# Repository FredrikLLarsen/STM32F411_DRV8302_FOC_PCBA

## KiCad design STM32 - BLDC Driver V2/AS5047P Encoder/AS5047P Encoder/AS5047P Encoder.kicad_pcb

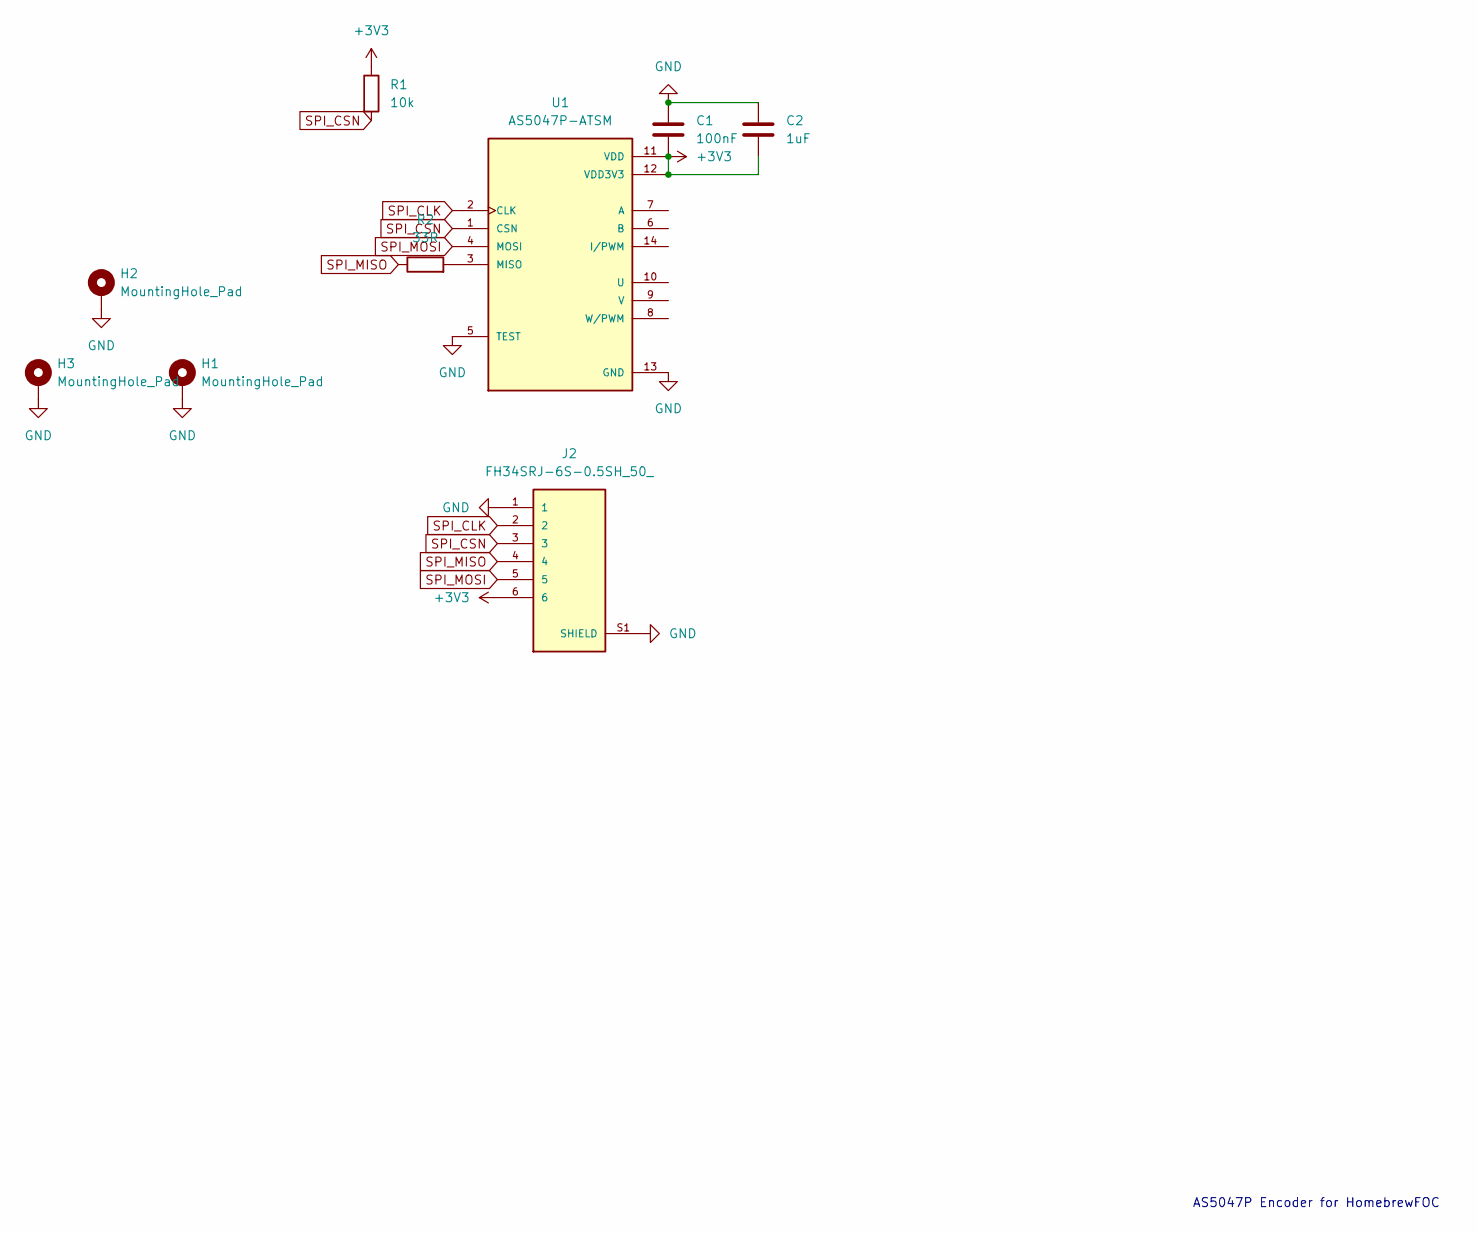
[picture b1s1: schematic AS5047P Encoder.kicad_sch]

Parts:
C1: 100nF; C_0603_1608Metric_Pad1.08x0.95mm_HandSolder
C2: 1uF; C_0603_1608Metric_Pad1.08x0.95mm_HandSolder
H1, H2, H3: MountingHole_Pad; MountingHole_3.2mm_M3_ISO7380_Pad
J2: FH34SRJ-6S-0.5SH_50_; HRS_FH34SRJ-6S-0.5SH_50_
R1: 10k; R_0603_1608Metric_Pad0.98x0.95mm_HandSolder
R2: 33R; R_0603_1608Metric_Pad0.98x0.95mm_HandSolder
U1: AS5047P-ATSM; SOP65P640X120-14N; PARTREV 1-01

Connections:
+3V3: C1.2, C2.2, J2.6, R1.1, U1.11 (VDD), U1.12 (VDD3V3)
GND: C1.1, C2.1, H1.1, H2.1, H3.1, J2.1, J2.S1 (SHIELD), J2.S2 (SHIELD), U1.5 (TEST), U1.13 (GND)
unnamed: R2.2, U1.3 (MISO)
SPI_CLK: J2.2, U1.2 (CLK)
SPI_CSN: J2.3, R1.2, U1.1 (CSN)
SPI_MISO: J2.4, R2.1
SPI_MOSI: J2.5, U1.4 (MOSI)

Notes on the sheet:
AS5047P Encoder for HomebrewFOC

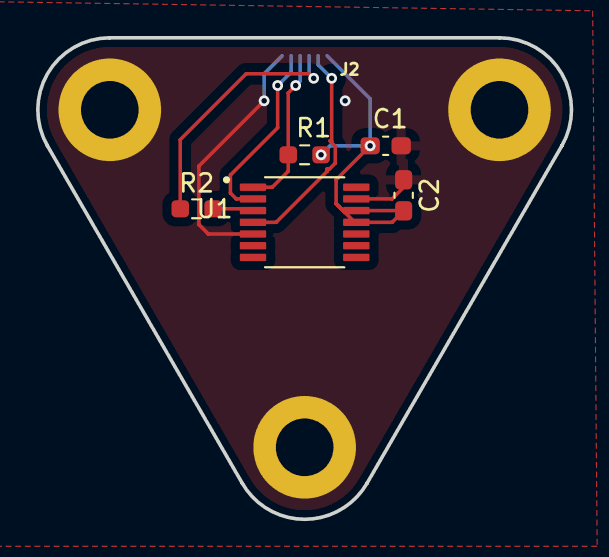
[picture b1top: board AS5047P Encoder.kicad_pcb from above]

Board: 2 copper layers, 29.7 x 26.8 mm, 9 parts (1 on the bottom side), 7 nets.

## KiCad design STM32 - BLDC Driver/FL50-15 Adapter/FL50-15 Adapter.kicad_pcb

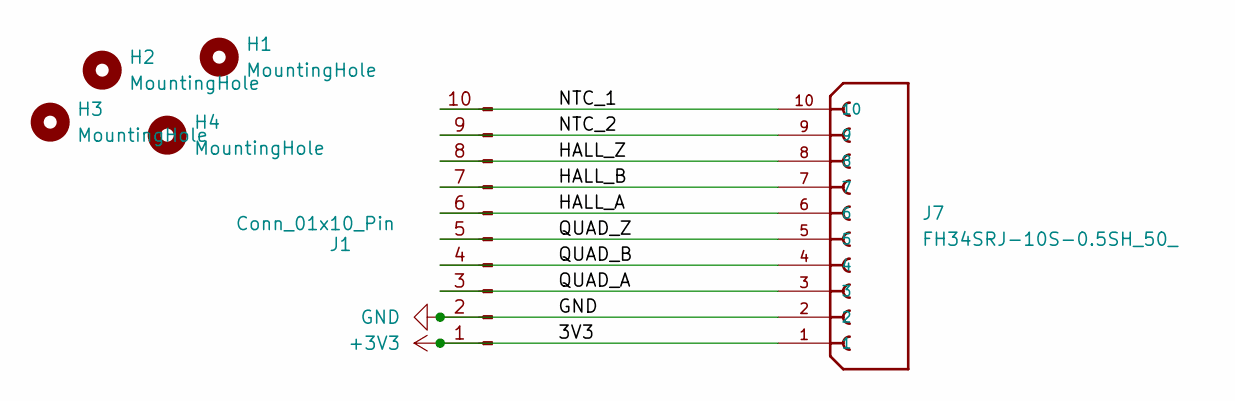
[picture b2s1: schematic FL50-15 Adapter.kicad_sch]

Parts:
H1, H2, H3, H4: MountingHole; MountingHole_3.2mm_M3
J1: Conn_01x10_Pin; PinHeader_1x10_P2.54mm_Vertical
J7: FH34SRJ-10S-0.5SH_50_; HRS_FH34SRJ-10S-0.5SH_50_; PARTREV Apr.1.2022

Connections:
+3V3: J1.1, J7.1
/HALL_A: J1.6, J7.6
/HALL_B: J1.7, J7.7
/HALL_Z: J1.8, J7.8
/NTC_1: J1.10, J7.10
/NTC_2: J1.9, J7.9
/QUAD_A: J1.3, J7.3
/QUAD_B: J1.4, J7.4
/QUAD_Z: J1.5, J7.5
GND: J1.2, J7.2

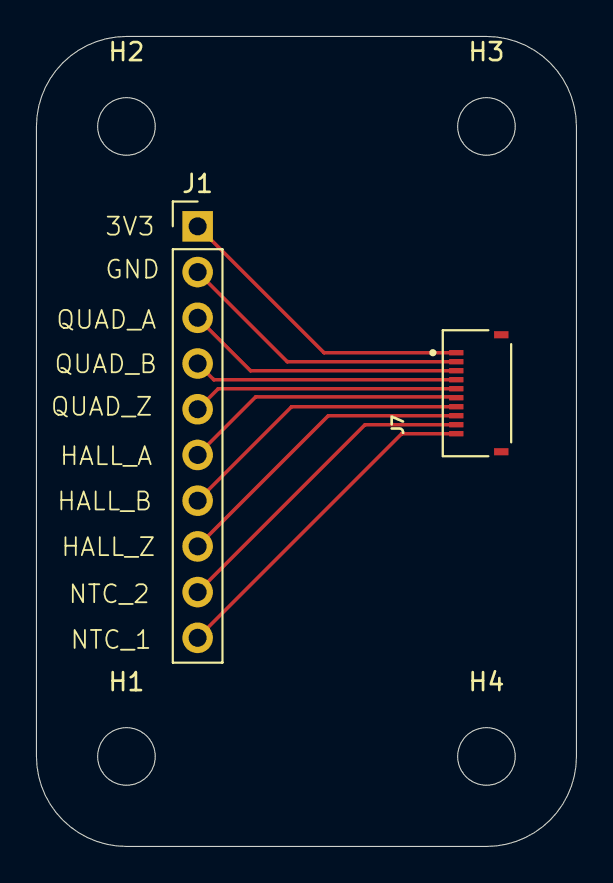
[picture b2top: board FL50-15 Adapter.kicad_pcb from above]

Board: 2 copper layers, 30.0 x 45.0 mm, 6 parts (0 on the bottom side), 10 nets.

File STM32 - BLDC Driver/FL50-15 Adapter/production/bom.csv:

Designator,Footprint,Quantity,Value,LCSC Part #
J1,PinHeader_1x10_P2.54mm_Vertical,1,Conn_01x10_Pin,
J7,HRS_FH34SRJ-10S-0.5SH_50_,1,FH34SRJ-10S-0.5SH_50_,

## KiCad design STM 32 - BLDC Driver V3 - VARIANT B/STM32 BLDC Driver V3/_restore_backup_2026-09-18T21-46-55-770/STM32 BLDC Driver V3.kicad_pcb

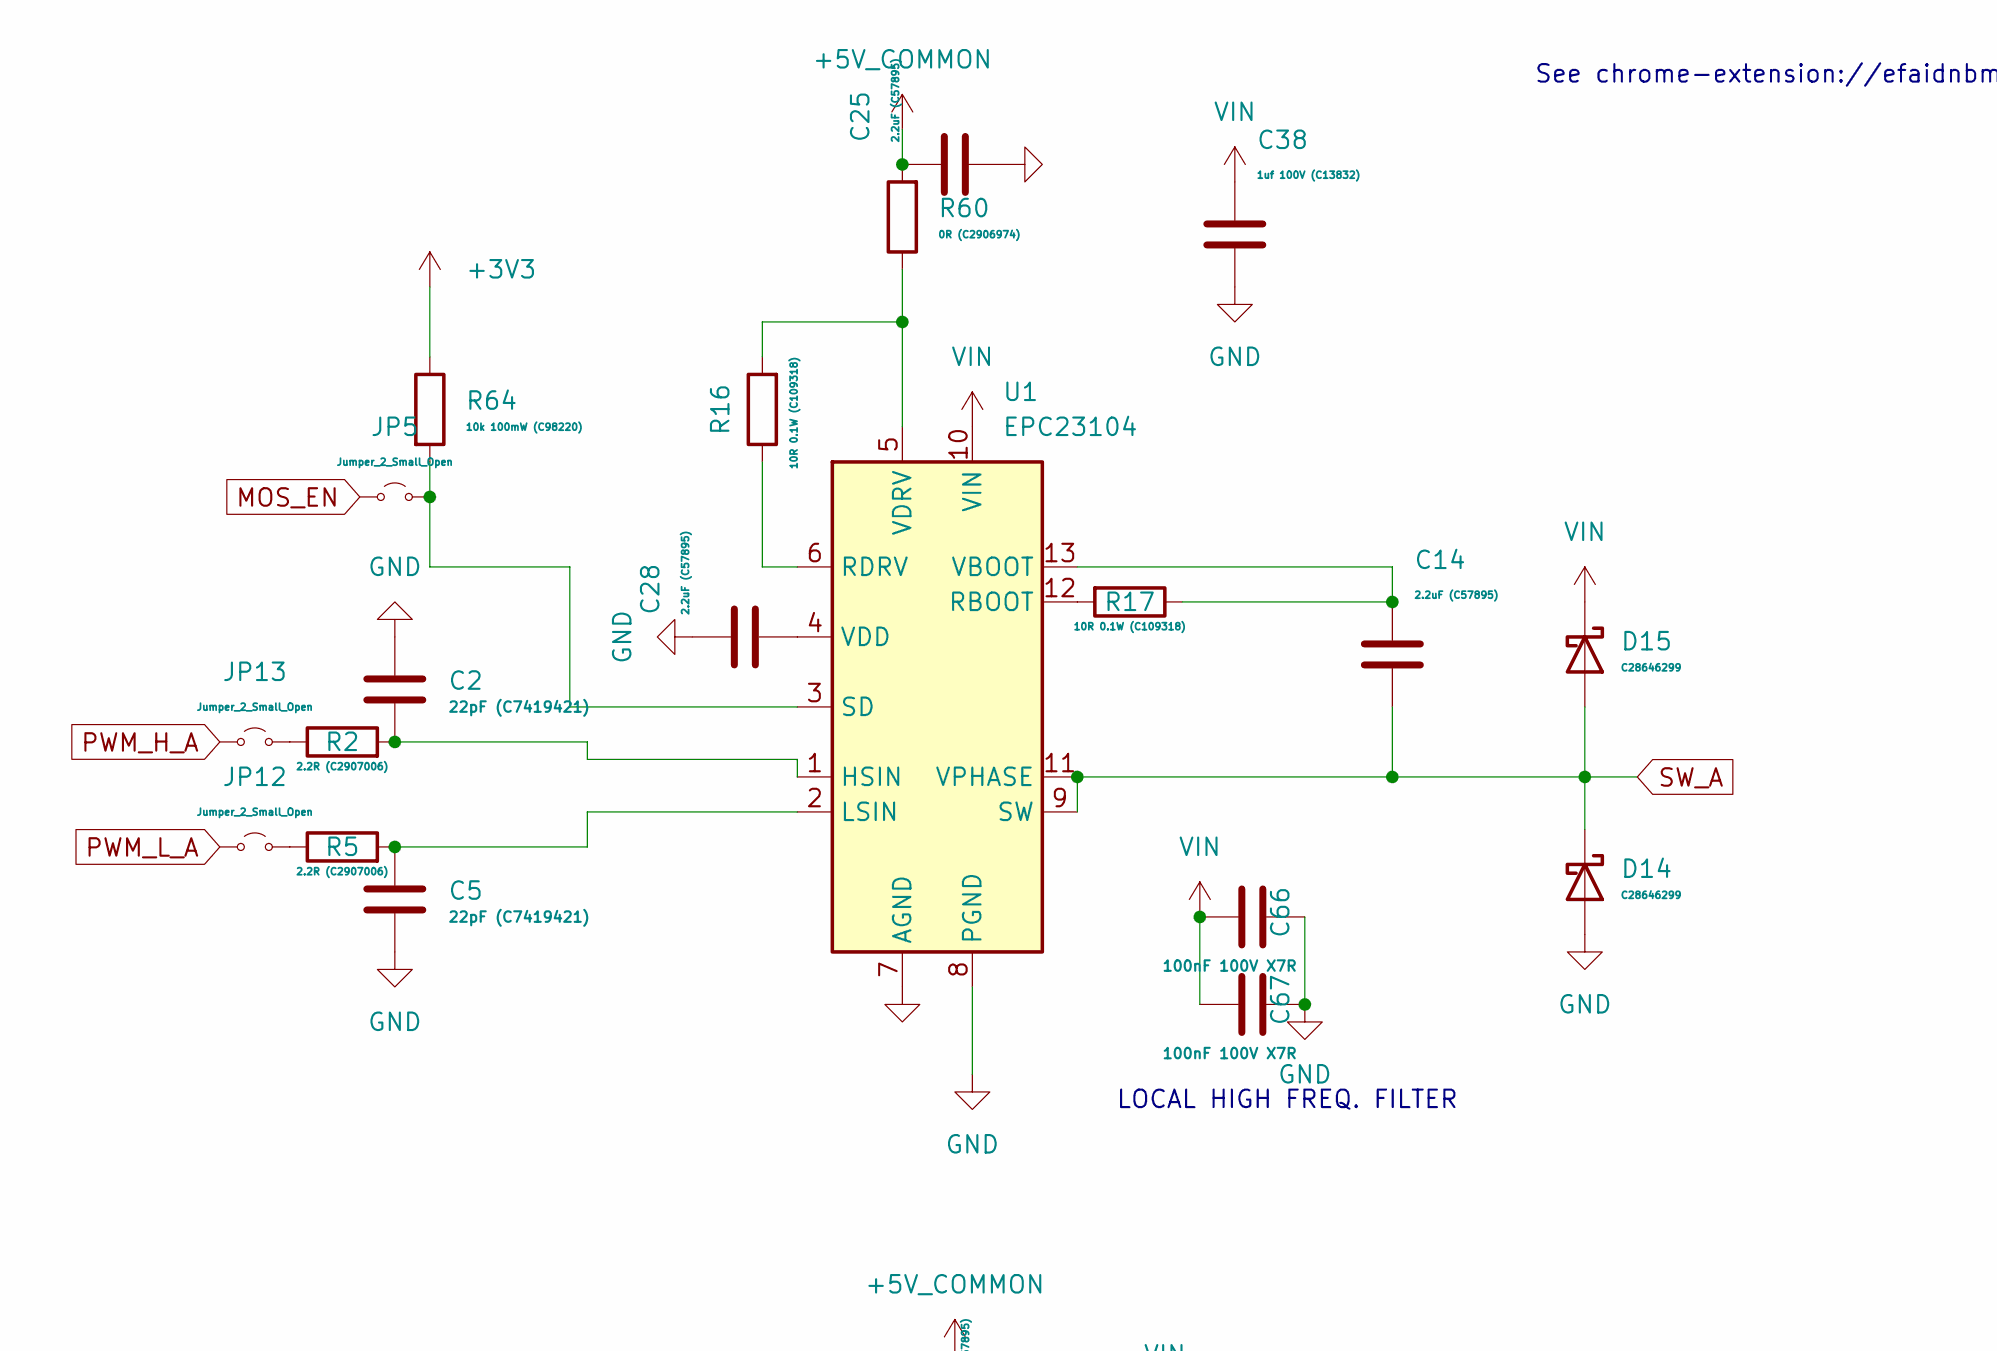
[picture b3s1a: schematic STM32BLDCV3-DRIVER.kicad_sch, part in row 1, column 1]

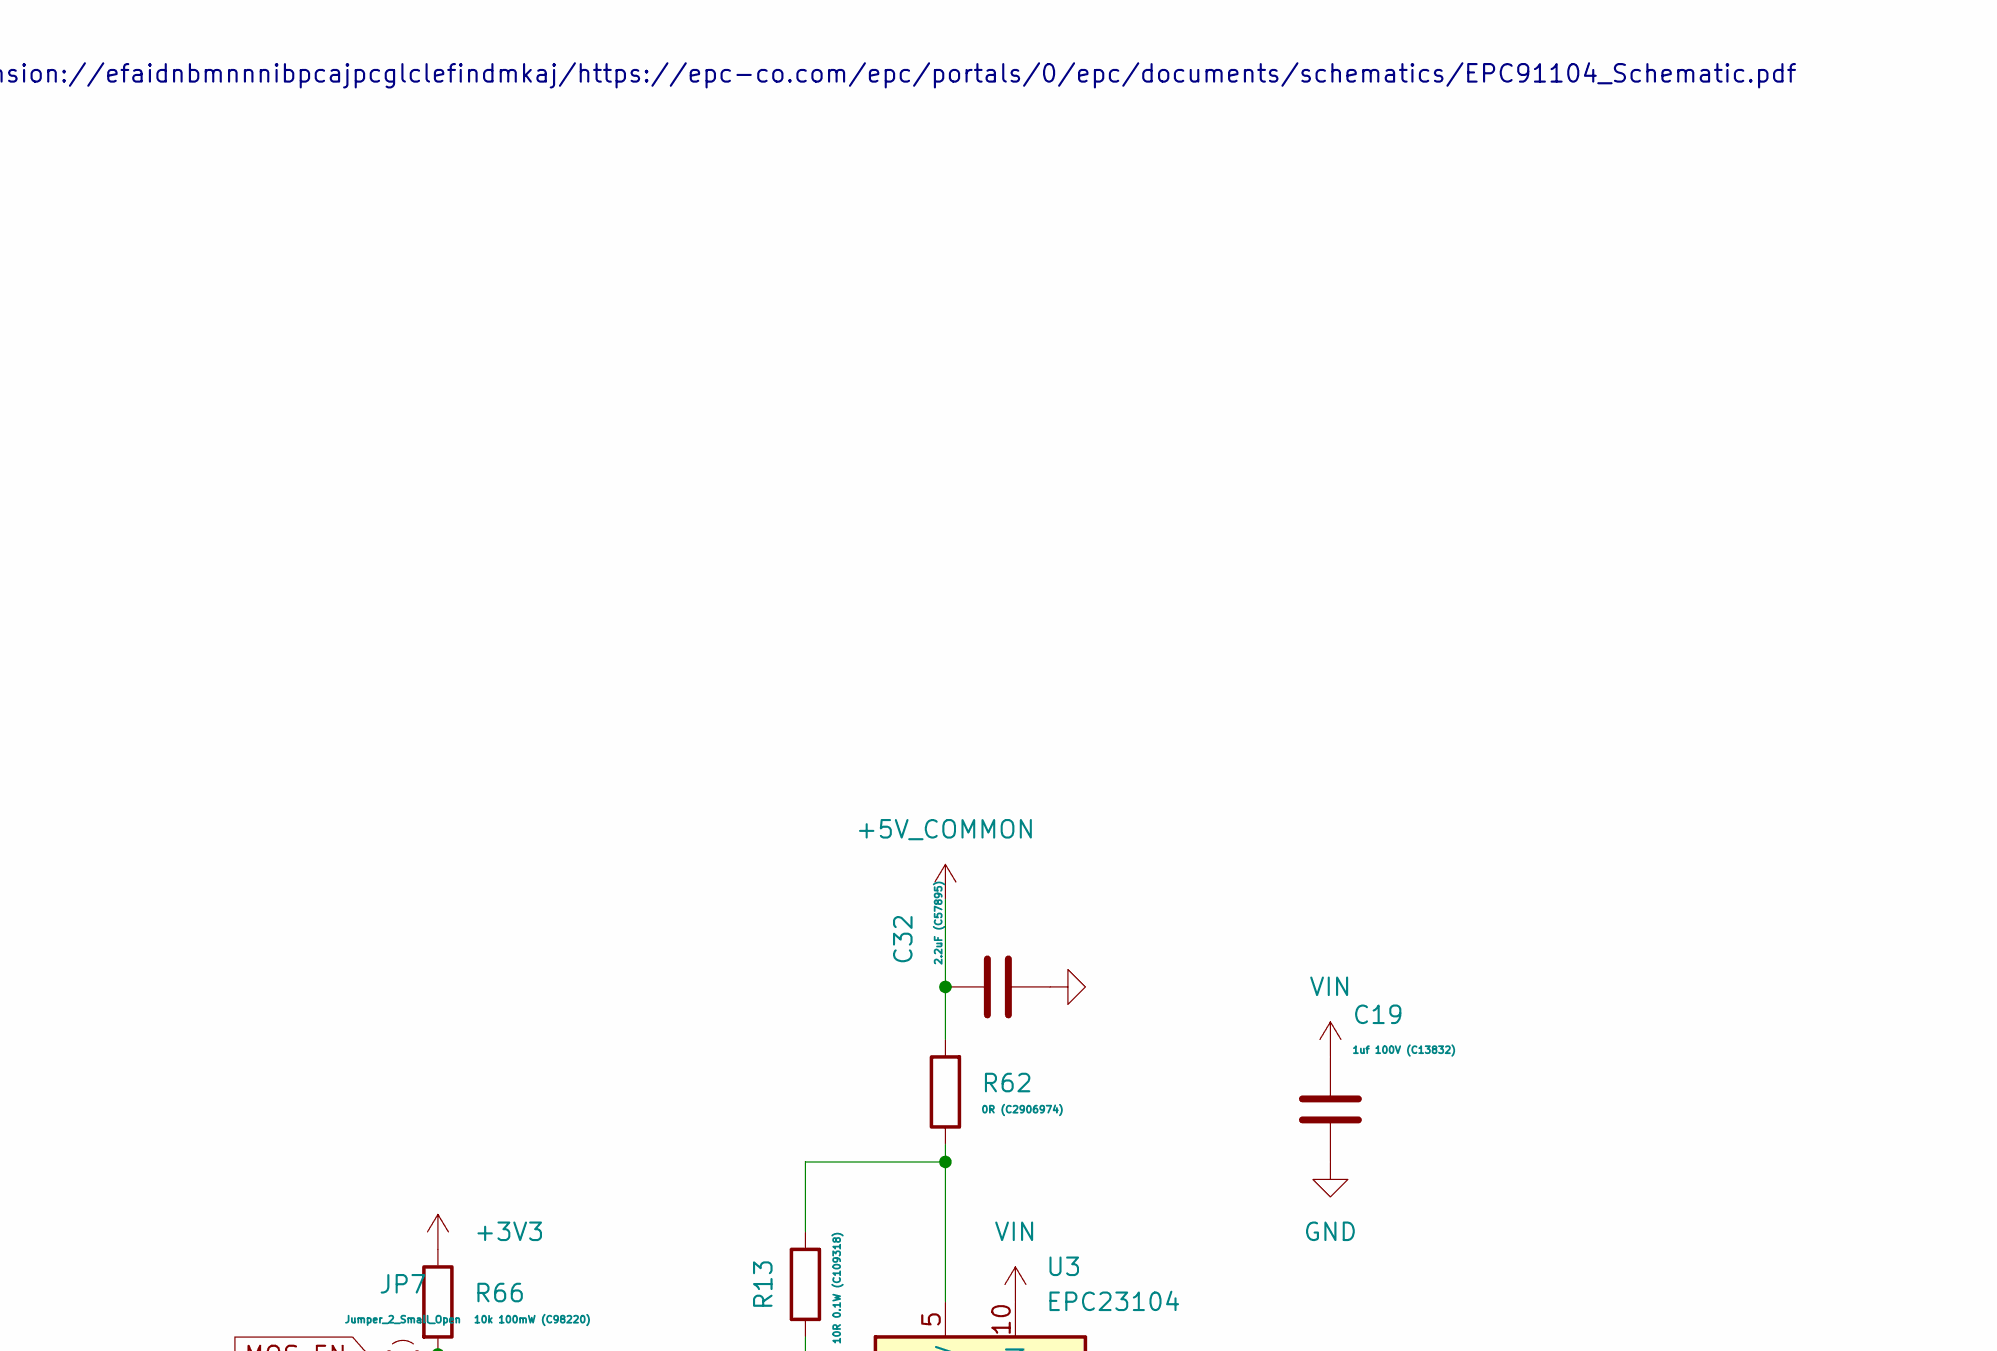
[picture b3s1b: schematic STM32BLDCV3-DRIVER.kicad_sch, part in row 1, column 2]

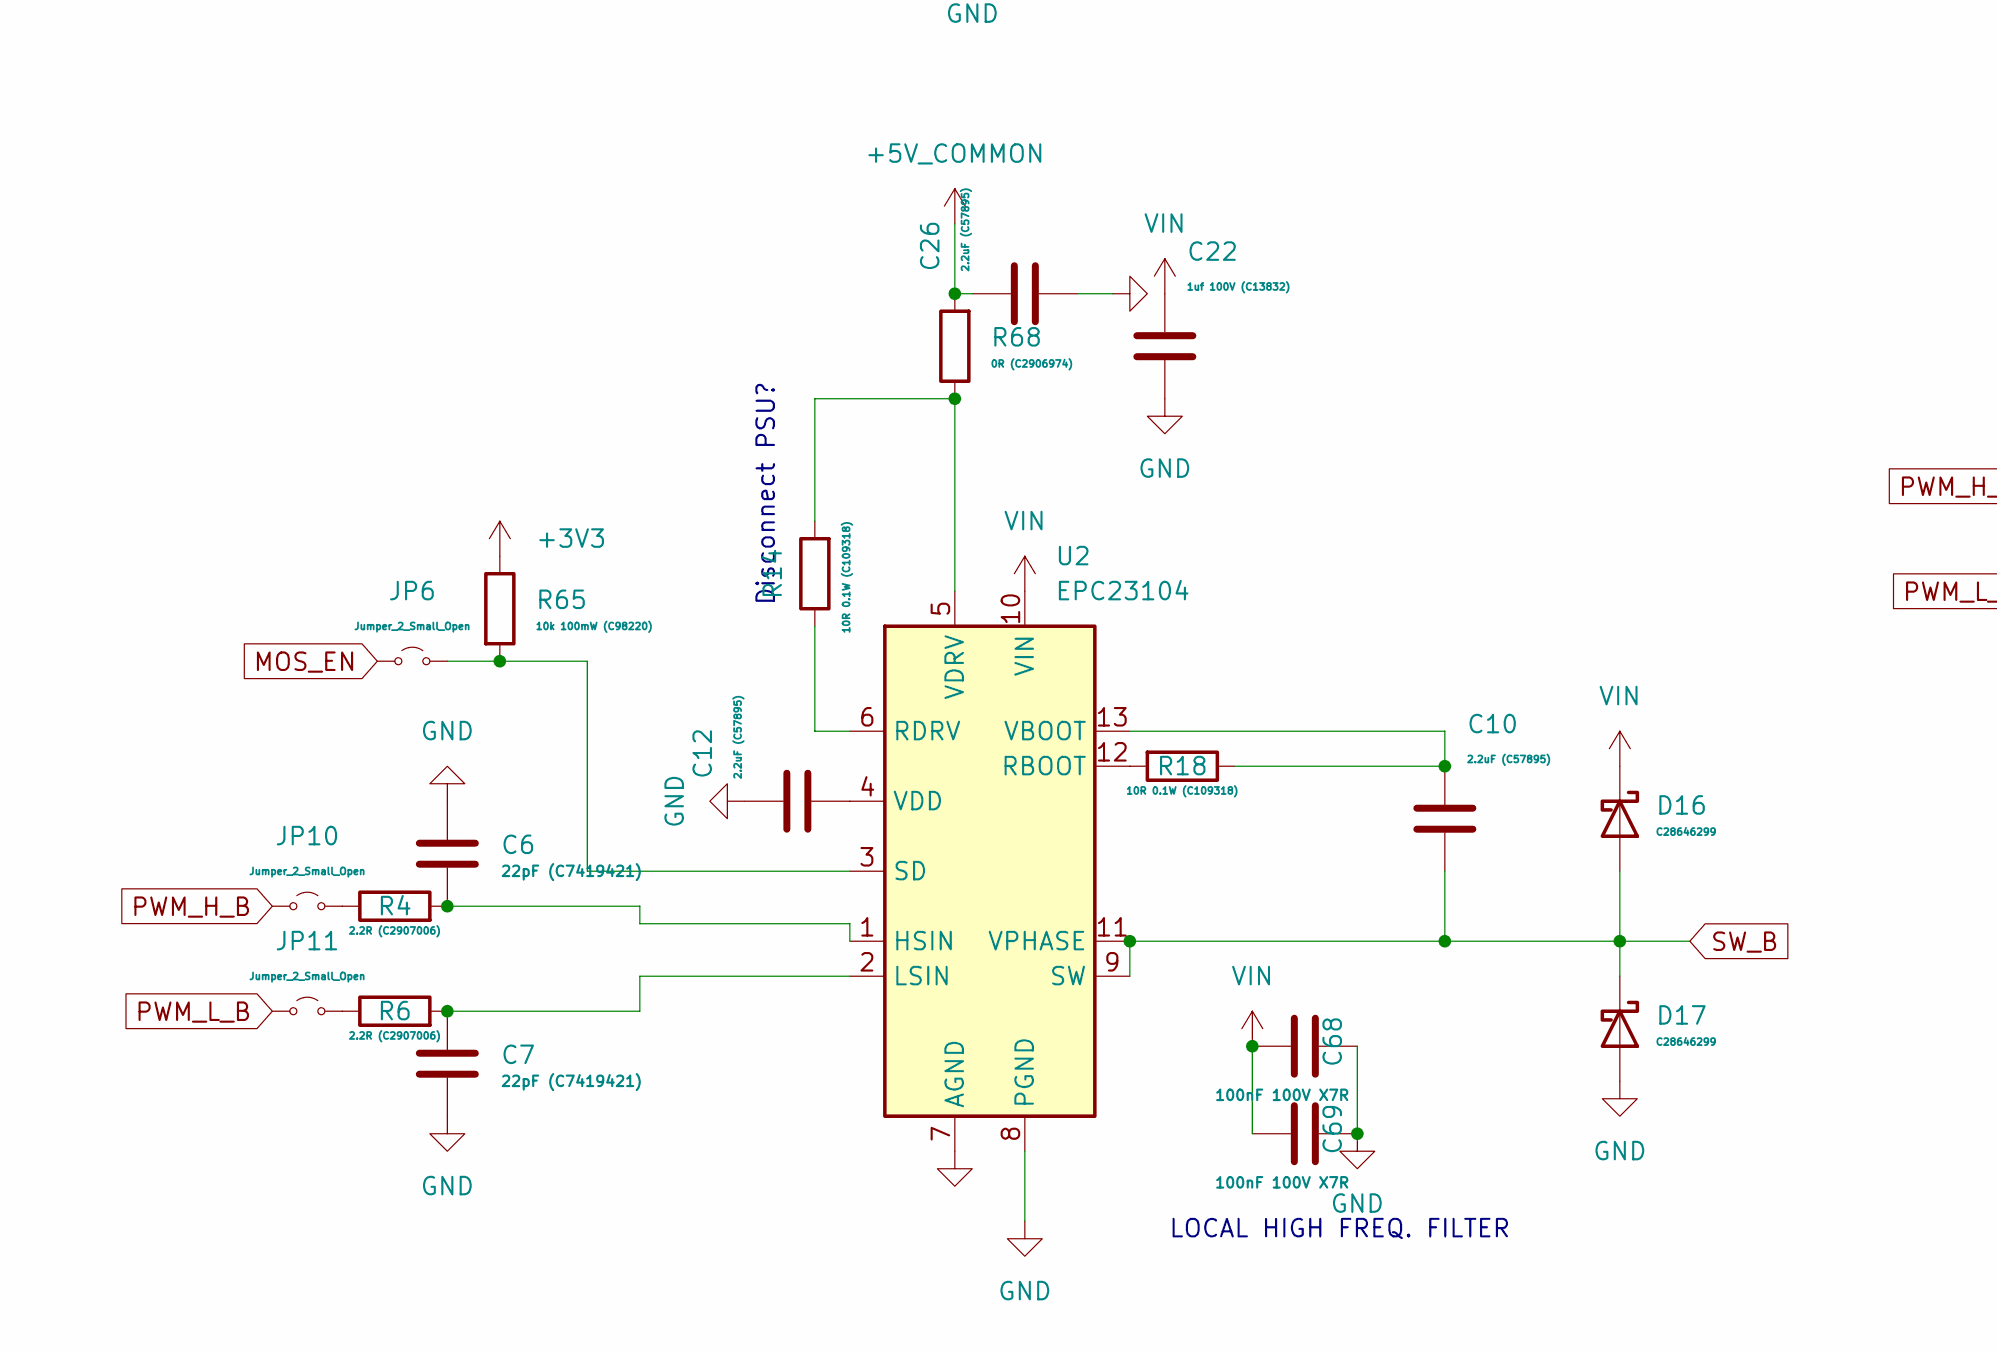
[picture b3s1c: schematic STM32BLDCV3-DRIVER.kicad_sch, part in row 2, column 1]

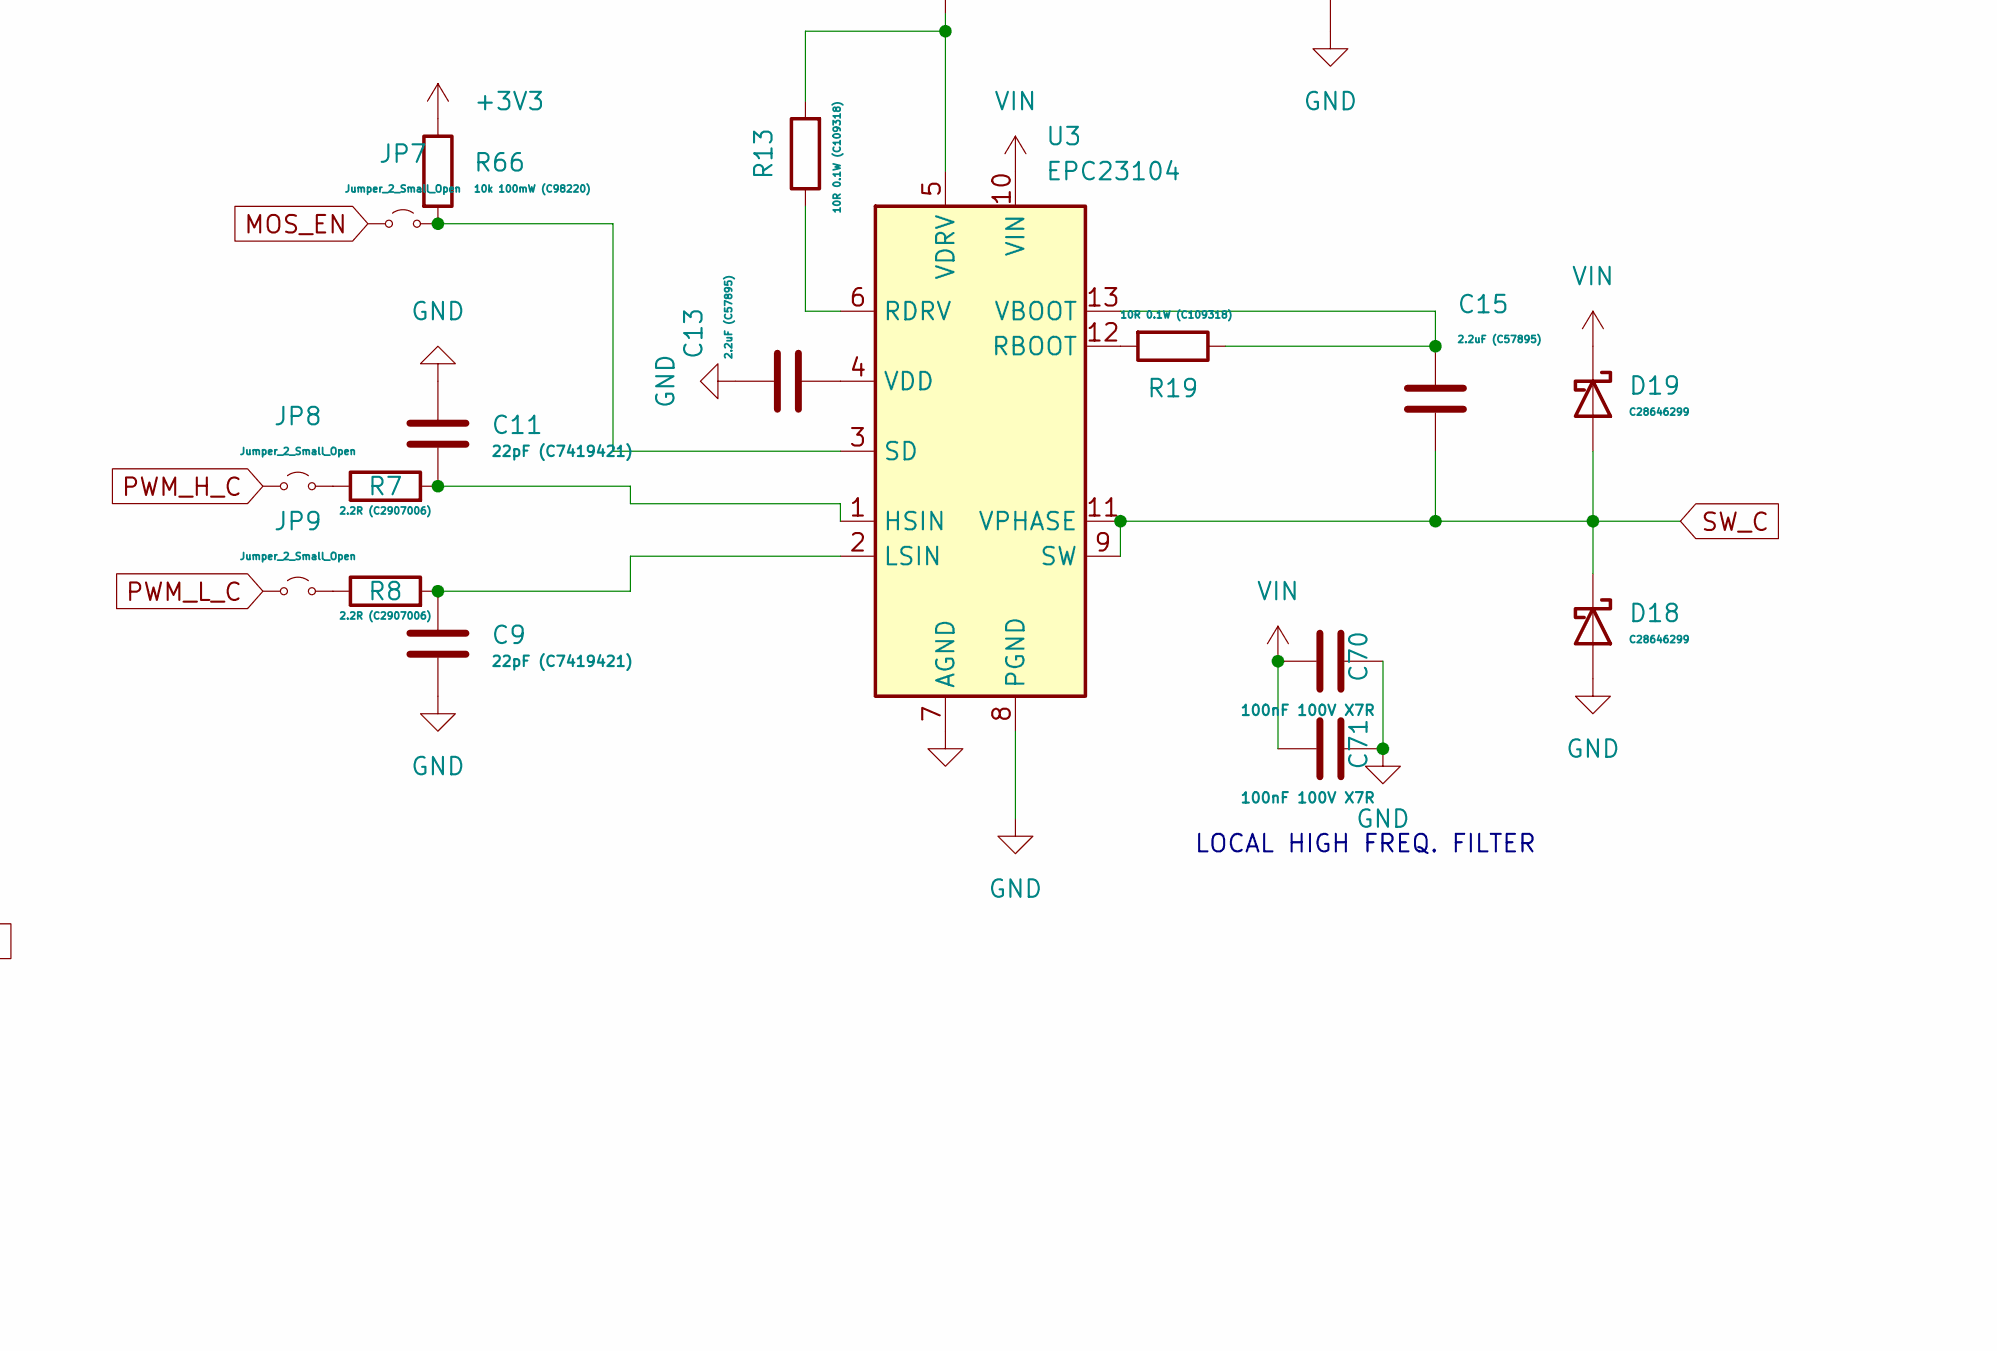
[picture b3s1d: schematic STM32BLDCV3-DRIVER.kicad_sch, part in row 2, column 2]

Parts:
C2, C5, C6, C7, C9, C11: 22pF (C7419421); C_0603_1608Metric_Pad1.08x0.95mm_HandSolder
C10, C12, C13, C14, C15, C25, C26, C28, C32: 2.2uF (C57895); C_0603_1608Metric_Pad1.08x0.95mm_HandSolder
C19, C22, C38: 1uf 100V (C13832); C_1206_3216Metric_Pad1.33x1.80mm_HandSolder
C66, C67, C68, C69, C70, C71: 100nF 100V X7R; C_0805_2012Metric_Pad1.18x1.45mm_HandSolder
D14, D15, D16, D17, D18, D19: C28646299; D_SMB
JP5, JP6, JP7, JP8, JP9, JP10, JP11, JP12, JP13: Jumper_2_Small_Open; SolderJumper-2_P1.3mm_Open_RoundedPad1.0x1.5mm
R2, R4, R5, R6, R7, R8: 2.2R (C2907006); R_0603_1608Metric_Pad0.98x0.95mm_HandSolder
R13, R14, R16, R17, R18, R19: 10R 0.1W (C109318); R_0603_1608Metric_Pad0.98x0.95mm_HandSolder
R60, R62, R68: 0R (C2906974); R_0603_1608Metric_Pad0.98x0.95mm_HandSolder
R64, R65, R66: 10k 100mW (C98220); R_0603_1608Metric_Pad0.98x0.95mm_HandSolder
U1, U2, U3: EPC23104; EPC_QFN-13-3EP_3.5x5mm_P0.5mm

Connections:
+3V3: R64.1, R65.1, R66.1; also elsewhere on the board
+5V_COMMON: C25.1, C26.1, C32.1, R60.2, R62.2, R68.2; also elsewhere on the board
GND: C2.1, C5.2, C6.1, C7.2, C9.2, C11.1, C12.1, C13.1, C19.2, C22.2, C25.2, C26.2, C28.1, C32.2, C38.2, C66.1, C67.1, C68.1, C69.1, C70.1, C71.1, D14.2 (A), D17.2 (A), D18.2 (A), U1.7 (AGND), U1.8 (PGND), U2.7 (AGND), U2.8 (PGND), U3.7 (AGND), U3.8 (PGND); also elsewhere on the board
MOS_EN: JP5.1 (A), JP6.1 (A), JP7.1 (A); also elsewhere on the board
unnamed: JP5.2 (B), R64.2, U1.3 (SD)
unnamed: JP6.2 (B), R65.2, U2.3 (SD)
unnamed: JP7.2 (B), R66.2, U3.3 (SD)
unnamed: JP8.2 (B), R7.1
unnamed: JP9.2 (B), R8.1
unnamed: JP10.2 (B), R4.1
unnamed: JP11.2 (B), R6.1
unnamed: JP12.2 (B), R5.1
unnamed: JP13.2 (B), R2.1
unnamed: C2.2, R2.2, U1.1 (HSIN)
unnamed: C5.1, R5.2, U1.2 (LSIN)
unnamed: R17.2, U1.12 (RBOOT)
unnamed: R16.1, U1.6 (RDRV)
unnamed: C14.1, R17.1, U1.13 (VBOOT)
unnamed: C28.2, U1.4 (VDD)
unnamed: R16.2, R60.1, U1.5 (VDRV)
unnamed: C6.2, R4.2, U2.1 (HSIN)
unnamed: C7.1, R6.2, U2.2 (LSIN)
unnamed: R18.2, U2.12 (RBOOT)
unnamed: R14.1, U2.6 (RDRV)
unnamed: C10.1, R18.1, U2.13 (VBOOT)
unnamed: C12.2, U2.4 (VDD)
unnamed: R14.2, R68.1, U2.5 (VDRV)
unnamed: C11.2, R7.2, U3.1 (HSIN)
unnamed: C9.1, R8.2, U3.2 (LSIN)
unnamed: R19.2, U3.12 (RBOOT)
unnamed: R13.1, U3.6 (RDRV)
unnamed: C15.1, R19.1, U3.13 (VBOOT)
unnamed: C13.2, U3.4 (VDD)
unnamed: R13.2, R62.1, U3.5 (VDRV)
PWM_H_A: JP13.1 (A); also elsewhere on the board
PWM_H_B: JP10.1 (A); also elsewhere on the board
PWM_H_C: JP8.1 (A); also elsewhere on the board
PWM_L_A: JP12.1 (A); also elsewhere on the board
PWM_L_B: JP11.1 (A); also elsewhere on the board
PWM_L_C: JP9.1 (A); also elsewhere on the board
SW_A: C14.2, D14.1 (K), D15.2 (A), U1.9 (SW), U1.11 (VPHASE); also elsewhere on the board
SW_B: C10.2, D16.2 (A), D17.1 (K), U2.9 (SW), U2.11 (VPHASE); also elsewhere on the board
SW_C: C15.2, D18.1 (K), D19.2 (A), U3.9 (SW), U3.11 (VPHASE); also elsewhere on the board
VIN: C19.1, C22.1, C38.1, C66.2, C67.2, C68.2, C69.2, C70.2, C71.2, D15.1 (K), D16.1 (K), D19.1 (K), U1.10 (VIN), U2.10 (VIN), U3.10 (VIN); also elsewhere on the board

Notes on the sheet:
See chrome-extension://efaidnbmnnnibpcajpcglclefindmkaj/https://epc-co.com/epc/portals/0/epc/documents/schematics/EPC91104_Schematic.pdf
LOCAL HIGH FREQ. FILTER
Disconnect PSU?

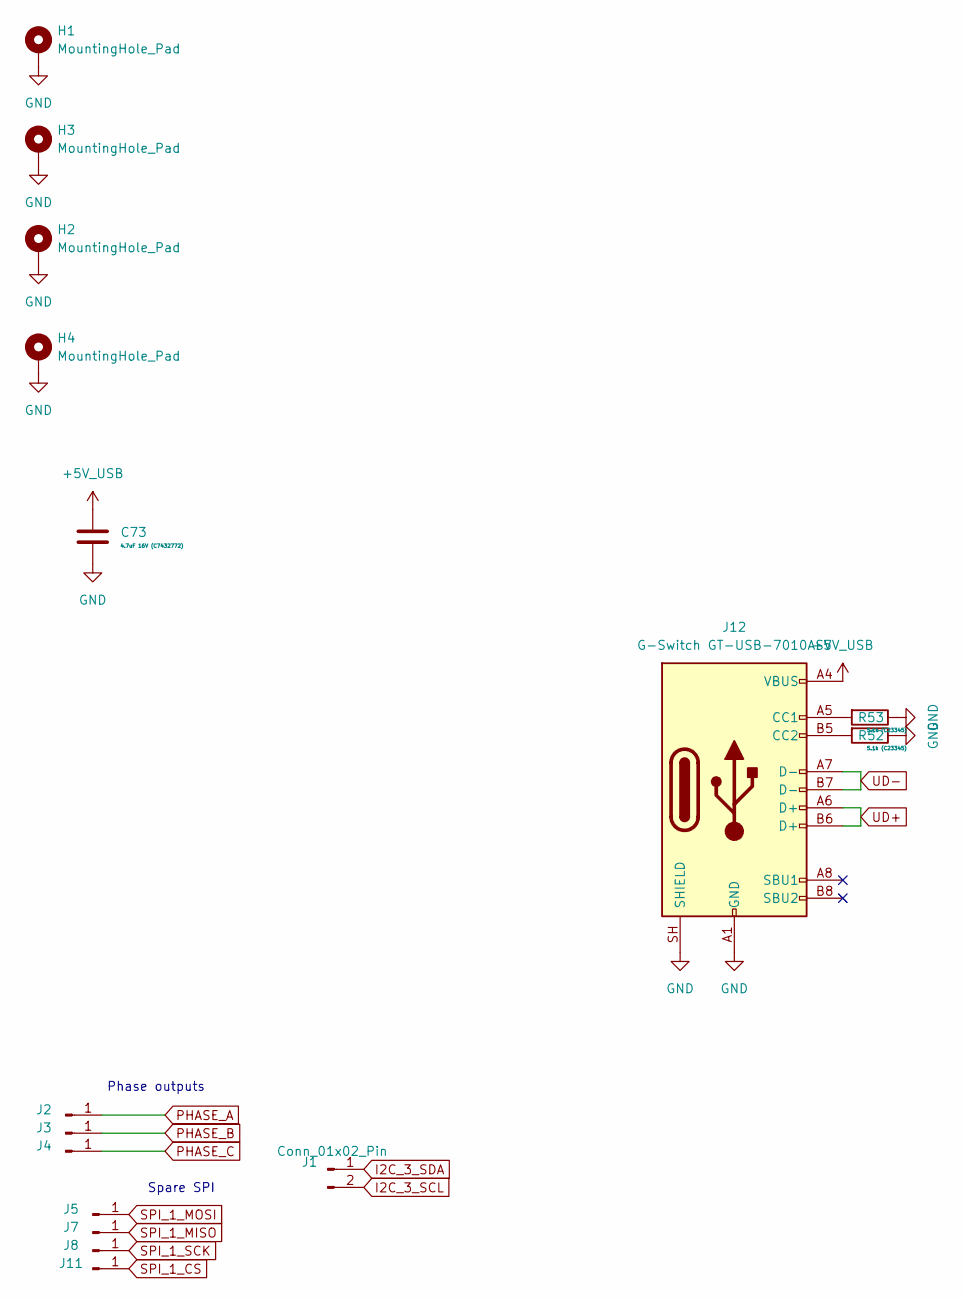
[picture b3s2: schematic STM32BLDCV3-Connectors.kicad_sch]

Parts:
C73: 4.7uF 16V (C7432772); C_0603_1608Metric_Pad1.08x0.95mm_HandSolder
H1, H2, H3, H4: MountingHole_Pad; MountingHole_2.2mm_M2_Pad_Via
J1: Conn_01x02_Pin; PinHeader_1x02_P2.54mm_Vertical
J2, J3, J4: Conn_01x01_Pin; STICHED SOLDER PAD
J5, J7, J8, J11: Conn_01x01_Pin; STICHED SOLDER PAD_SMALL
J12: G-Switch GT-USB-7010ASV; USB_C_Receptacle_G-Switch_GT-USB-7010ASV
R52, R53: 5.1k (C23345); R_0603_1608Metric_Pad0.98x0.95mm_HandSolder

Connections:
+5V_USB: C73.1, J12.A4 (VBUS), J12.A9 (VBUS), J12.B4 (VBUS), J12.B9 (VBUS); also elsewhere on the board
GND: C73.2, H1.1 (1_1), H2.1 (1_1), H3.1 (1_1), H4.1 (1_1), J12.A1 (GND), J12.A12 (GND), J12.B1 (GND), J12.B12 (GND), J12.SH (SHIELD), R52.1, R53.1; also elsewhere on the board
I2C_3_SCL: J1.2; also elsewhere on the board
I2C_3_SDA: J1.1; also elsewhere on the board
unnamed: J12.A5 (CC1), R53.2
unnamed: J12.B5 (CC2), R52.2
PHASE_A: J2.1 (Pin_1_1); also elsewhere on the board
PHASE_B: J3.1 (Pin_1_1); also elsewhere on the board
PHASE_C: J4.1 (Pin_1_1); also elsewhere on the board
SPI_1_CS: J11.1 (Pin_1_1); also elsewhere on the board
SPI_1_MISO: J7.1 (Pin_1_1); also elsewhere on the board
SPI_1_MOSI: J5.1 (Pin_1_1); also elsewhere on the board
SPI_1_SCK: J8.1 (Pin_1_1); also elsewhere on the board
UD+: J12.A6 (D+), J12.B6 (D+); also elsewhere on the board
UD-: J12.A7 (D-), J12.B7 (D-); also elsewhere on the board

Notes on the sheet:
Phase outputs
Spare SPI
